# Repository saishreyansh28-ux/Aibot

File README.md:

# Aibot

A bot that has AI in it.

 It connects to your api key and runs the AI
 You replace the code placeholder labeled API, WiFi information with your details and upload to the device.

I made it because I feel it would be easier if you had a desk buddy sort of thing beside you to help you with connecting with your AI.

 It runs using an:
 
 *ESP32 S3 Mini
 
 *OLED
 
 *Microphone
 
 *Speaker
 
 *Audio Amplifier

 #CASE

The Oled shows the answer in text on the screen and we can speak to the AI model using the Microphone.

It answers using the speaker
If you cannot hear the words properly, you can alternatively use the OLED Display for the response.

#SCHEMATIC

#Parts Footprints:

*INMP441(Microphone)

*ESP32-S3-MINI-1(Microcontroller)

*ER_OLEDM0.91_1x-I2C(Display)

*BQ76952PFB(Battery Management System)

*MAX98357A(Audio Amplifier)

#USAGE

While uploading the provided code to the microcontroller, edit the placeholders. Enter your WiFi Information and the Place Holder for Api Key and AI model.

If running a local llm, take the api key provided by the llm and paste it there and edit the AI model with the one you are running.

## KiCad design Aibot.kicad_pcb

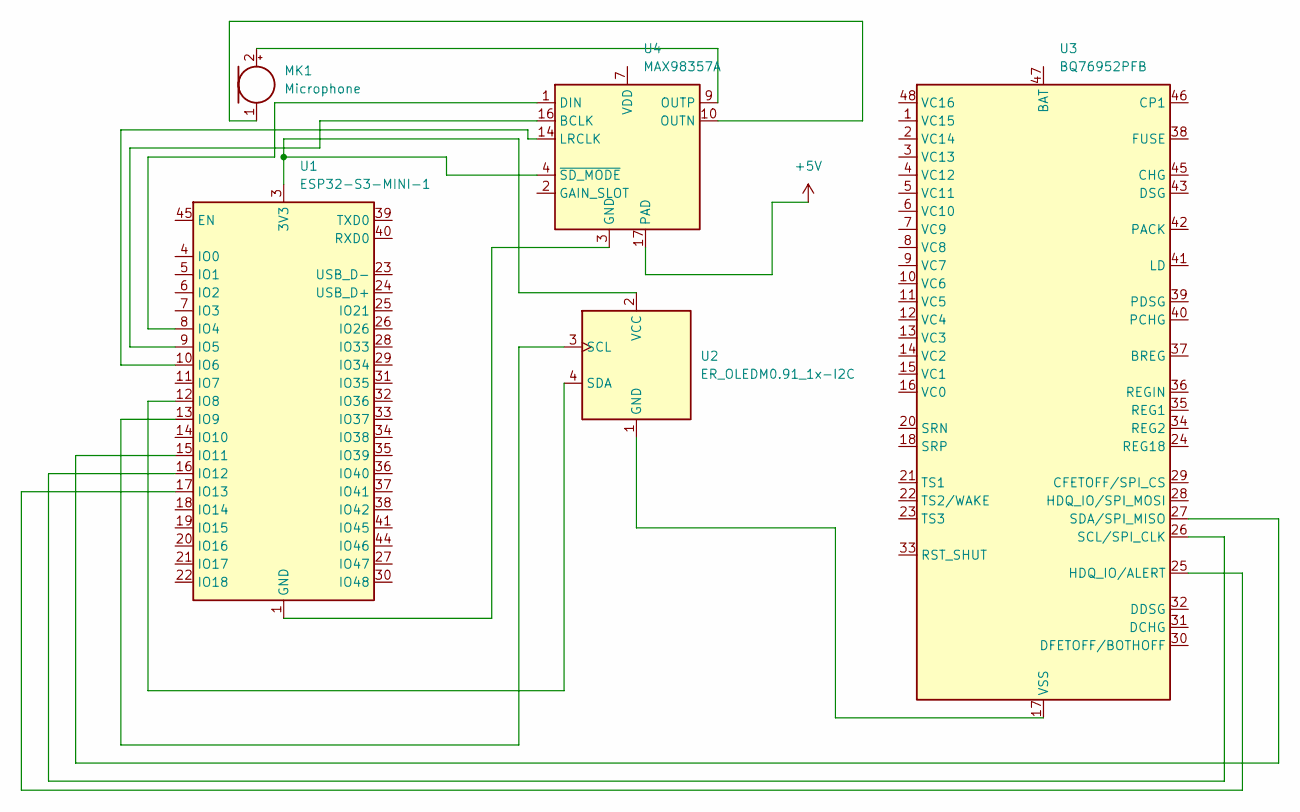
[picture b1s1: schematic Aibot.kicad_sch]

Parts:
MK1: Microphone; Sanyo_STK4xx-15_78.0x8.0mm_P2.54mm
U1: ESP32-S3-MINI-1; ESP32-S2-MINI-1
U2: ER_OLEDM0.91_1x-I2C
U3: BQ76952PFB; TQFP-48_7x7mm_P0.5mm
U4: MAX98357A; TQFN-16-1EP_3x3mm_P0.5mm_EP1.23x1.23mm

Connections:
+5V: U4.17 (PAD)
unnamed: MK1.2 (+), U4.9 (OUTP)
unnamed: MK1.1 (-), U4.10 (OUTN)
unnamed: U1.3 (3V3), U2.2 (VCC), U4.4 (~SD_MODE)
unnamed: U1.1 (GND), U1.2 (GND), U1.42 (GND), U1.43 (GND), U1.46 (GND), U1.47 (GND), U1.48 (GND), U1.49 (GND), U1.50 (GND), U1.51 (GND), U1.52 (GND), U1.53 (GND), U1.54 (GND), U1.55 (GND), U1.56 (GND), U1.57 (GND), U1.58 (GND), U1.59 (GND), U1.60 (GND), U1.61 (GND), U1.62 (GND), U1.63 (GND), U1.64 (GND), U1.65 (GND), U4.3 (GND), U4.11 (GND), U4.15 (GND)
unnamed: U1.8 (IO4), U4.1 (DIN)
unnamed: U1.9 (IO5), U4.16 (BCLK)
unnamed: U1.10 (IO6), U4.14 (LRCLK)
unnamed: U1.12 (IO8), U2.4 (SDA)
unnamed: U1.13 (IO9), U2.3 (SCL)
unnamed: U1.15 (IO11), U3.27 (SDA/SPI_MISO)
unnamed: U1.16 (IO12), U3.26 (SCL/SPI_CLK)
unnamed: U1.17 (IO13), U3.25 (HDQ_IO/ALERT)
unnamed: U2.1 (GND), U3.17 (VSS)
unnamed: U4.7 (VDD), U4.8 (VDD)

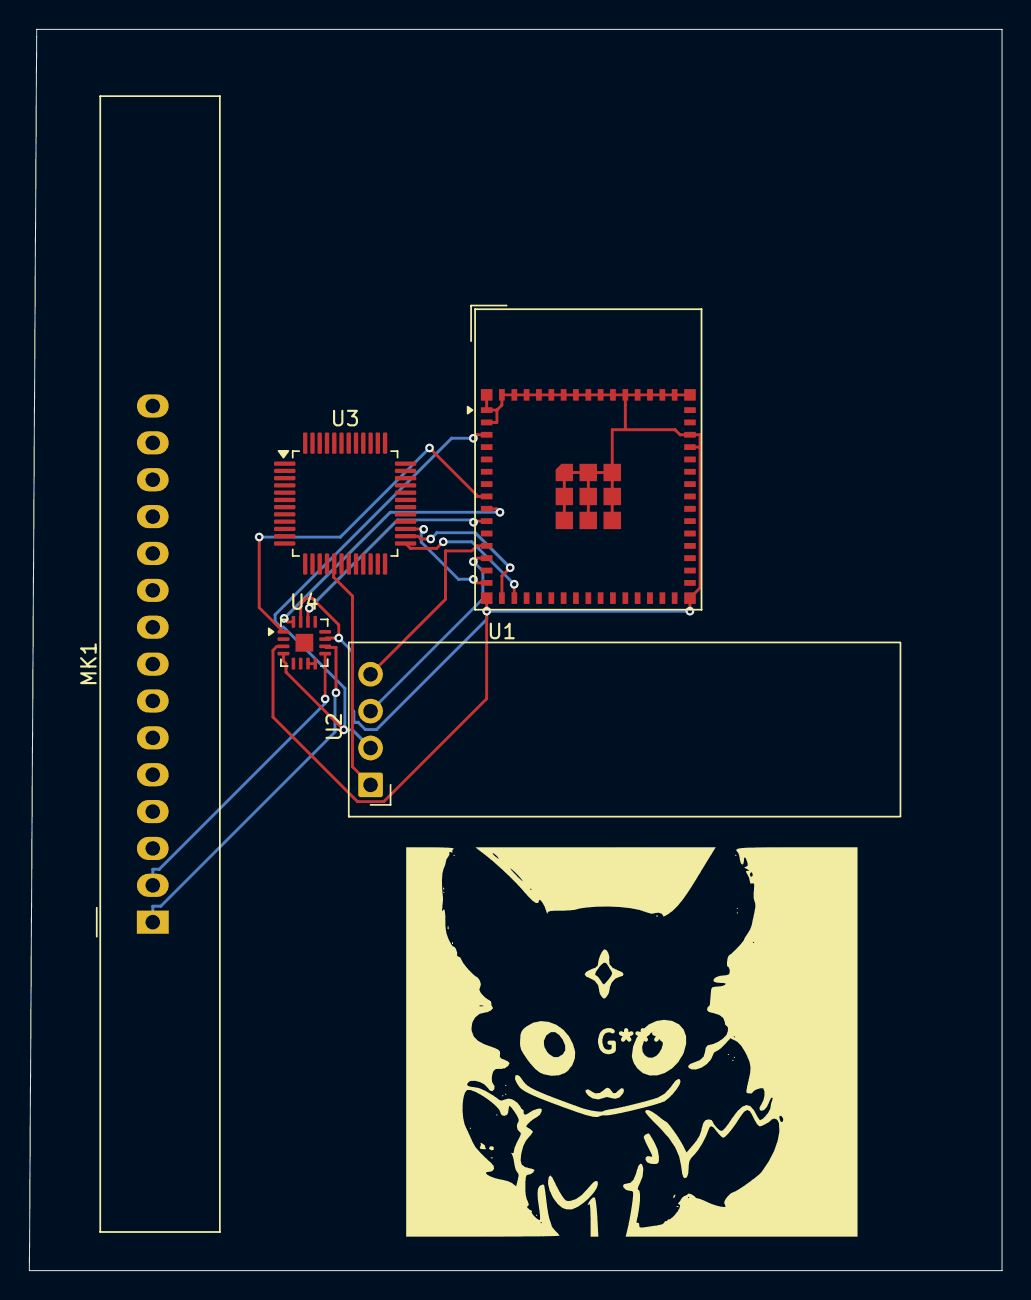
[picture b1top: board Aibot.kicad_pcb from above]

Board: 2 copper layers, 67.0 x 85.5 mm, 5 parts (0 on the bottom side), 14 nets.

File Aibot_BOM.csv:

Id,Designator,Footprint,Quantity,Designation,Supplier and ref,,
1,MK1,Sanyo_STK4xx-15_78.0x8.0mm_P2.54mm,1,Microphone,https://www.amazon.in/Oceanlabz-INMP441-Omnidirectional-Micr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,,
2,U1,ESP32-S2-MINI-1,1,ESP32-S3-MINI-1,https://www.amazon.in/RoboThings-ESP32-S3-Supermini-Bluetoot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,,
3,U2,ER_OLEDM0.91_1x-I2C,1,ER_OLEDM0.91_1x-I2C,https://robu.in/product/0-91-inch-128x32-i2c-iic-serial-blue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,,
4,U3,TQFP-48_7x7mm_P0.5mm,1,BQ76952PFB,https://www.ti.com/product/BQ76952/part-details/BQ76952PFBR,,
5,U4,TQFN-16-1EP_3x3mm_P0.5mm_EP1.23x1.23mm,1,MAX98357A,https://robu.in/product/adafruit-max98357a-i2s-3w-class-d-am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,,
